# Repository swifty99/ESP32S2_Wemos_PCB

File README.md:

# ESP32S2_Wemos_PCB
Handy adapter to make use of all the IO.
ESP Devices have so many nice interfaces. This PCB adds:
- protection due to dumbness (serial 100Ohms save you electronics big time)
- nice plugs XH plugs work great
- protect against magic smoke from dumb inverse power
- add MosFETs to switch fast and reliable without extra hardwere
- select different power levels for connectors with solder jumpers

This is a Kicad project, feel free to improve. Or just upload the pcb file to the manufacturer you like

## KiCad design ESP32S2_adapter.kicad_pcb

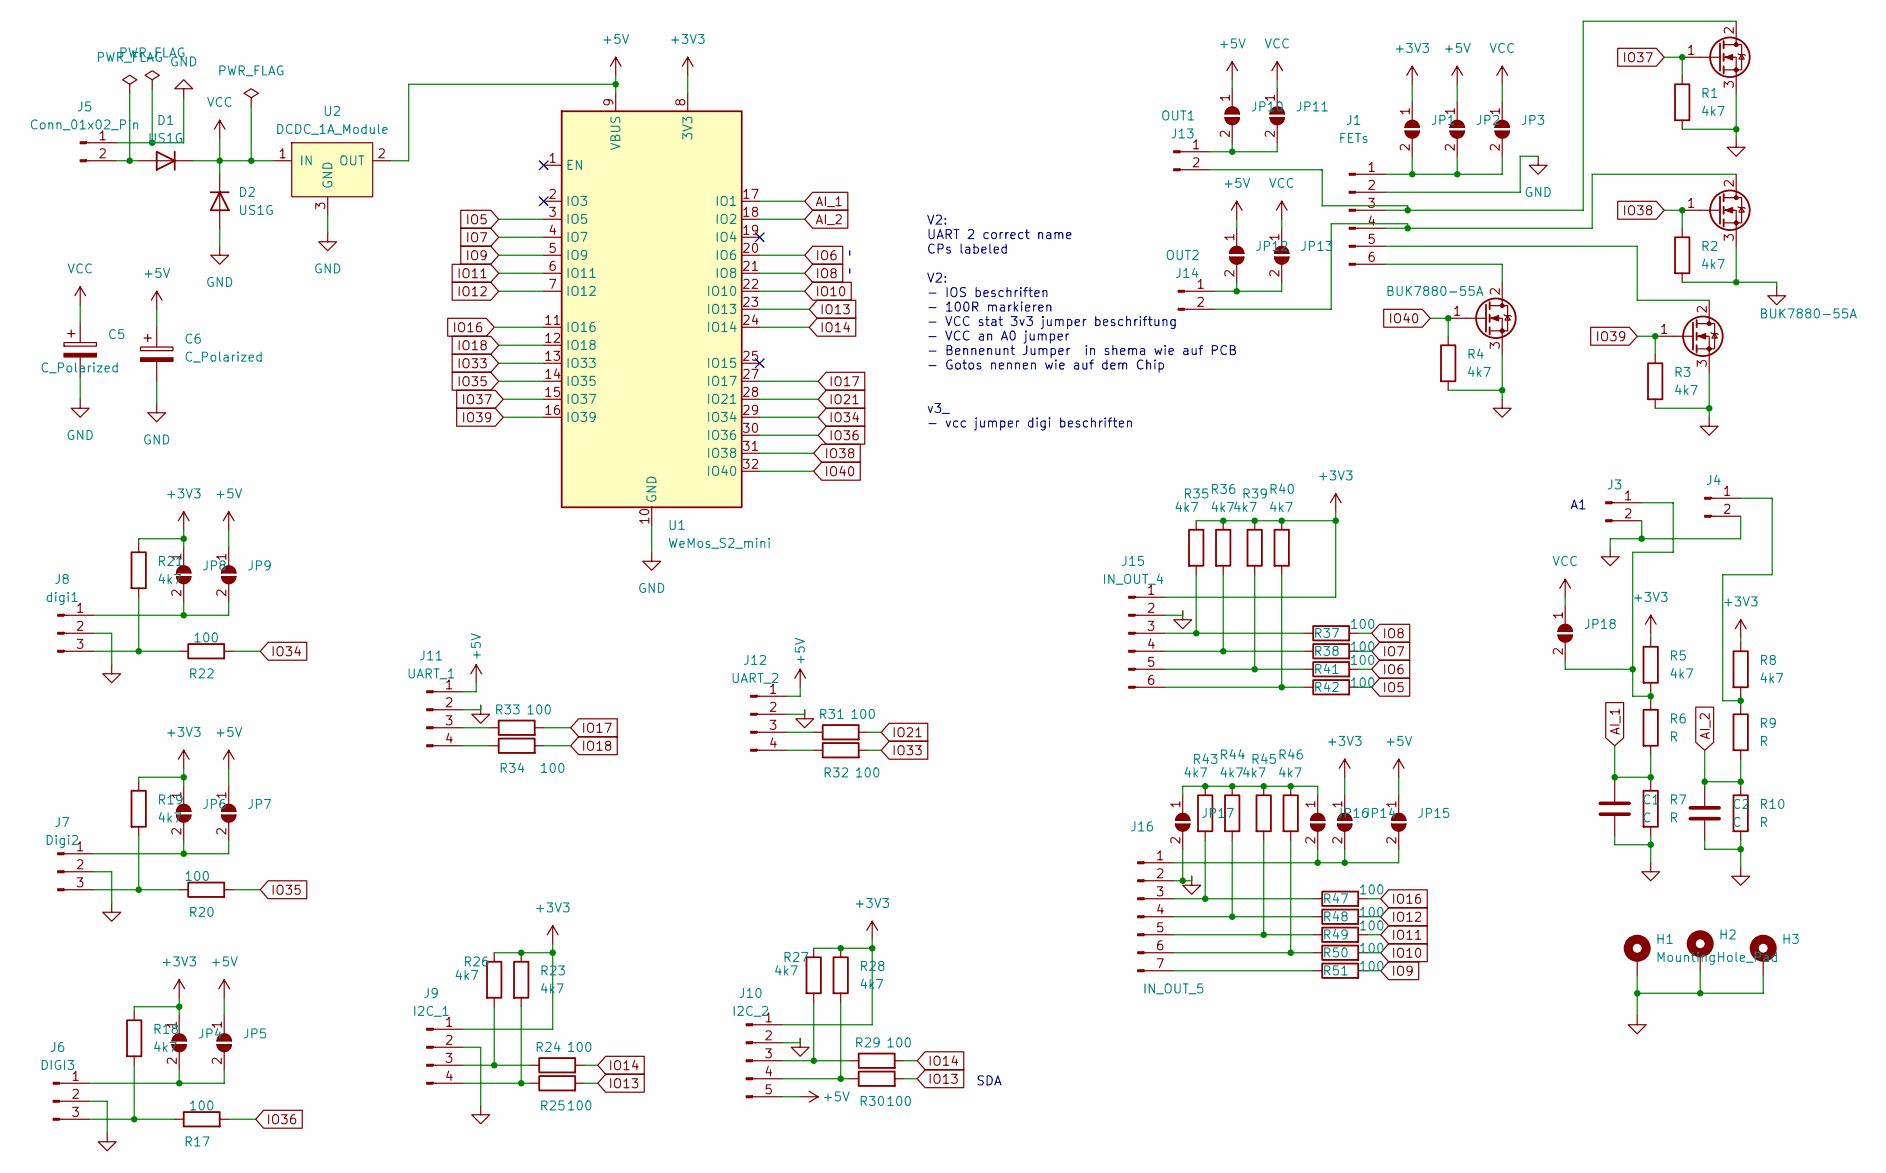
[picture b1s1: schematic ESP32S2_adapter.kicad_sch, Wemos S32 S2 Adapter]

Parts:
C1, C2: C; C_0805_2012Metric_Pad1.18x1.45mm_HandSolder
C5, C6: C_Polarized; CP_Radial_D10.0mm_P3.80mm
D1, D2: US1G; D_SMA_Handsoldering
H1, H2, H3: MountingHole_Pad; MountingHole_3.5mm_Pad_Via
J1: FETs; JST_XH_B6B-XH-A_1x06_P2.50mm_Vertical
J3: A0; JST_XH_B2B-XH-A_1x02_P2.50mm_Vertical
J4: A1; JST_XH_B2B-XH-A_1x02_P2.50mm_Vertical
J5: Conn_01x02_Pin; AMASS_XT30U-M_1x02_P5.0mm_Vertical
J6: DIGI3; JST_XH_B3B-XH-A_1x03_P2.50mm_Vertical
J7: Digi2; JST_XH_B3B-XH-A_1x03_P2.50mm_Vertical
J8: digi1; JST_XH_B3B-XH-A_1x03_P2.50mm_Vertical
J9: I2C_1; JST_XH_B4B-XH-A_1x04_P2.50mm_Vertical
J10: I2C_2; JST_XH_B5B-XH-A_1x05_P2.50mm_Vertical
J11: UART_1; JST_XH_B4B-XH-A_1x04_P2.50mm_Vertical
J12: UART_2; JST_XH_B4B-XH-A_1x04_P2.50mm_Vertical
J13: OUT1; JST_XH_B2B-XH-A_1x02_P2.50mm_Vertical
J14: OUT2; JST_XH_B2B-XH-A_1x02_P2.50mm_Vertical
J15: IN_OUT_4; JST_XH_B6B-XH-A_1x06_P2.50mm_Vertical
J16: IN_OUT_5; JST_XH_B7B-XH-A_1x07_P2.50mm_Vertical
JP1, JP4, JP6, JP8, JP14: 3V3; SolderJumper-2_P1.3mm_Open_TrianglePad1.0x1.5mm
JP2, JP5, JP7, JP9, JP10, JP12, JP15: 5V; SolderJumper-2_P1.3mm_Open_TrianglePad1.0x1.5mm
JP3, JP13, JP18: VCC; SolderJumper-2_P1.3mm_Open_TrianglePad1.0x1.5mm
JP11, JP16: SolderJumper_2_Open; SolderJumper-2_P1.3mm_Open_TrianglePad1.0x1.5mm
JP17: GND; SolderJumper-2_P1.3mm_Open_TrianglePad1.0x1.5mm
Q1, Q2, Q3, Q4: BUK7880-55A; SOT-223-3_TabPin2
R1, R2, R3, R4, R5, R8, R18, R19, R21, R23, R26, R27, R28, R35, R36, R39, R40, R43, R44, R45, R46: 4k7; R_0805_2012Metric_Pad1.20x1.40mm_HandSolder
R6, R7, R9, R10: R; R_0805_2012Metric_Pad1.20x1.40mm_HandSolder
R17, R20, R22, R24, R25, R29, R30, R31, R32, R33, R34, R37, R38, R41, R42, R47, R48, R49, R50, R51: 100; R_0805_2012Metric_Pad1.20x1.40mm_HandSolder
U1: WeMos_S2_mini; WEMOS_S2_mini
U2: DCDC_1A_Module; DCDC_1A_module_bonded

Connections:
+3V3: J9.1, J10.1, J15.1, JP1.1 (A), JP4.1 (A), JP6.1 (A), JP8.1 (A), JP14.1 (A), R5.1, R8.1, R18.1, R19.1, R21.1, R23.1, R26.1, R27.1, R28.1, R35.1, R36.1, R39.1, R40.1, U1.8 (3V3)
+5V: C6.1, J10.5, J11.1, J12.1, JP2.1 (A), JP5.1 (A), JP7.1 (A), JP9.1 (A), JP10.1 (A), JP12.1 (A), JP15.1 (A), U1.9 (VBUS), U2.2 (OUT)
AI_1: C1.1, R6.2, R7.1, U1.17 (IO1)
AI_2: C2.1, R9.2, R10.1, U1.18 (IO2)
GND: C1.2, C2.2, C5.2, C6.2, D2.2 (A), H1.1, H2.1, H3.1, J1.2, J3.2, J4.2, J5.1, J6.2, J7.2, J8.2, J9.2, J10.2, J11.2, J12.2, J15.2, J16.2, JP17.2 (B), Q1.3 (S), Q2.3 (S), Q3.3 (S), Q4.3 (S), R1.2, R2.2, R3.2, R4.2, R7.2, R10.2, U1.10 (GND), U1.26 (GND), U2.3 (GND)
IO5: R42.2, U1.3 (IO5)
IO6: R41.2, U1.20 (IO6)
IO7: R38.2, U1.4 (IO7)
IO8: R37.2, U1.21 (IO8)
IO9: R51.2, U1.5 (IO9)
IO10: R50.2, U1.22 (IO10)
IO11: R49.2, U1.6 (IO11)
IO12: R48.2, U1.7 (IO12)
IO13: R25.2, R30.2, U1.23 (IO13)
IO14: R24.2, R29.2, U1.24 (IO14)
IO16: R47.2, U1.11 (IO16)
IO17: R33.2, U1.27 (IO17)
IO18: R34.2, U1.12 (IO18)
IO21: R31.2, U1.28 (IO21)
IO33: R32.2, U1.13 (IO33)
IO34: R22.2, U1.29 (IO34)
IO35: R20.2, U1.14 (IO35)
IO36: R17.2, U1.30 (IO36)
IO37: Q1.1 (G), R1.1, U1.15 (IO37)
IO38: Q2.1 (G), R2.1, U1.31 (IO38)
IO39: Q3.1 (G), R3.1, U1.16 (IO39)
IO40: Q4.1 (G), R4.1, U1.32 (IO40)
unnamed: D1.2 (A), J5.2
unnamed: J1.1, JP1.2 (B), JP2.2 (B), JP3.2 (B)
unnamed: J1.3, J13.2, Q1.2 (D)
unnamed: J1.4, J14.2, Q2.2 (D)
unnamed: J1.5, Q3.2 (D)
unnamed: J1.6, Q4.2 (D)
unnamed: J3.1, JP18.2 (B), R5.2, R6.1
unnamed: J4.1, R8.2, R9.1
unnamed: J6.1, JP4.2 (B), JP5.2 (B)
unnamed: J6.3, R17.1, R18.2
unnamed: J7.1, JP6.2 (B), JP7.2 (B)
unnamed: J7.3, R19.2, R20.1
unnamed: J8.1, JP8.2 (B), JP9.2 (B)
unnamed: J8.3, R21.2, R22.1
unnamed: J9.3, R24.1, R26.2
unnamed: J9.4, R23.2, R25.1
unnamed: J10.3, R27.2, R29.1
unnamed: J10.4, R28.2, R30.1
unnamed: J11.3, R33.1
unnamed: J11.4, R34.1
unnamed: J12.3, R31.1
unnamed: J12.4, R32.1
unnamed: J13.1, JP10.2 (B), JP11.2 (B)
unnamed: J14.1, JP12.2 (B), JP13.2 (B)
unnamed: J15.3, R35.2, R37.1
unnamed: J15.4, R36.2, R38.1
unnamed: J15.5, R39.2, R41.1
unnamed: J15.6, R40.2, R42.1
unnamed: J16.1, JP14.2 (B), JP15.2 (B), JP16.2 (B)
unnamed: J16.3, R43.2, R47.1
unnamed: J16.4, R44.2, R48.1
unnamed: J16.5, R45.2, R49.1
unnamed: J16.6, R46.2, R50.1
unnamed: J16.7, R51.1
unnamed: JP16.1 (A), JP17.1 (A), R43.1, R44.1, R45.1, R46.1
VCC: C5.1, D1.1 (K), D2.1 (K), JP3.1 (A), JP11.1 (A), JP13.1 (A), JP18.1 (A), U2.1 (IN)

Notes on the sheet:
V2: UART 2 correct name CPs labeled V2: - IOS beschriften - 100R markieren - VCC stat 3v3 jumper beschriftung - VCC an A0 jumper - Bennenunt Jumper in shema wie auf PCB - Gotos nennen wie auf dem Chip v3_ - vcc jumper digi beschriften
SDA

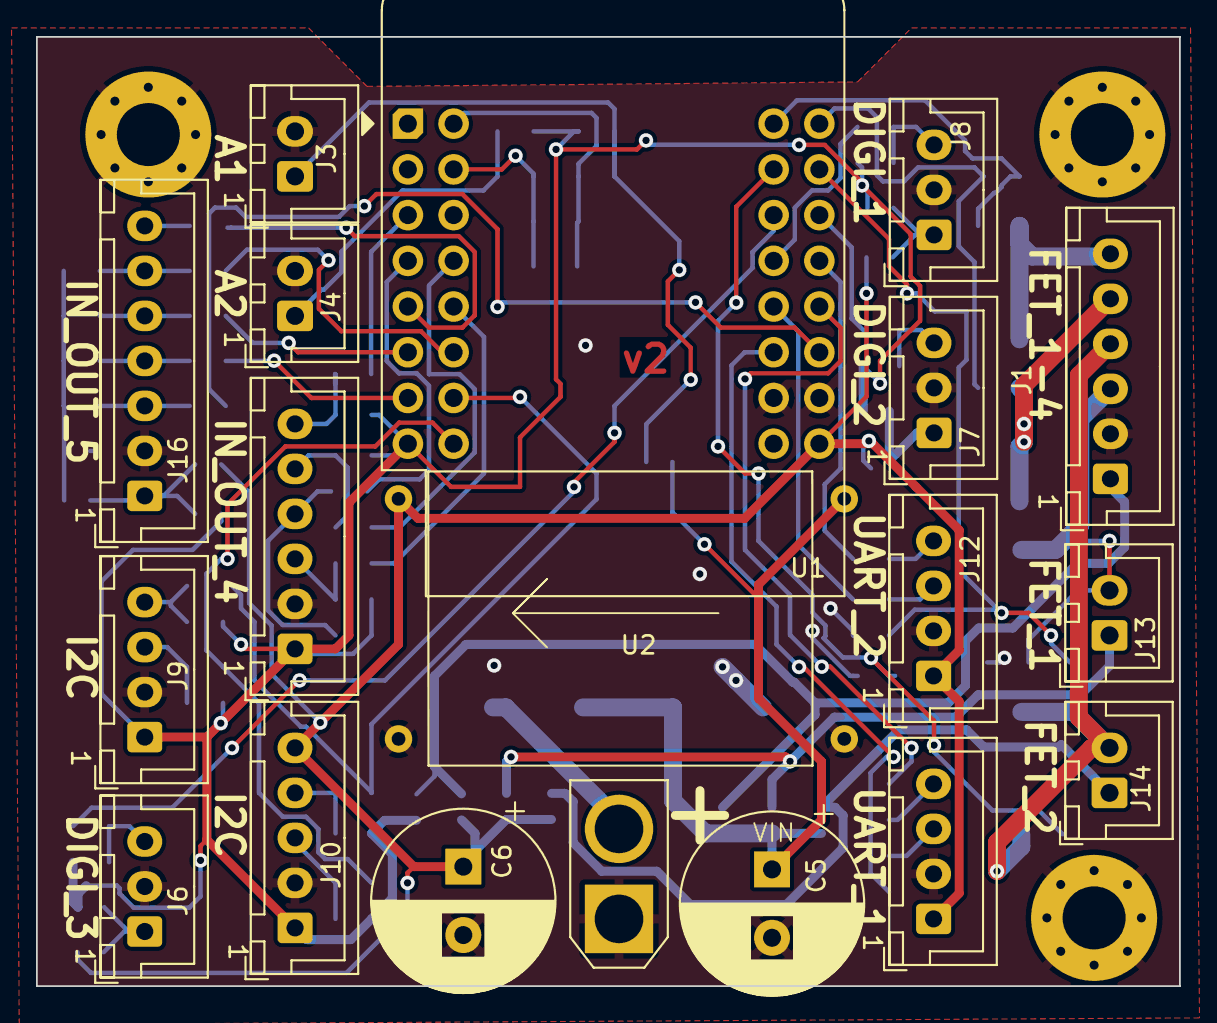
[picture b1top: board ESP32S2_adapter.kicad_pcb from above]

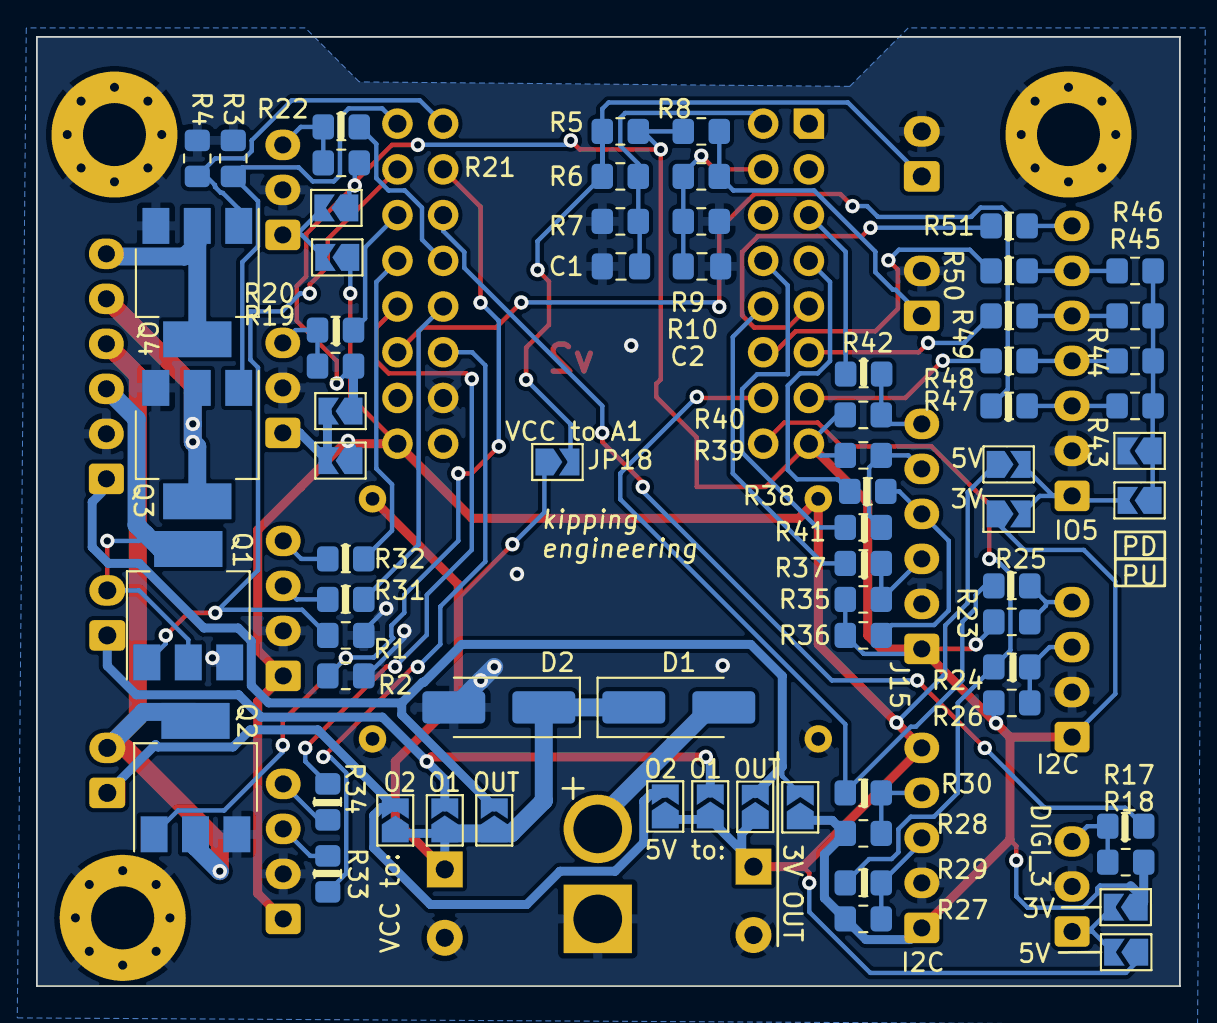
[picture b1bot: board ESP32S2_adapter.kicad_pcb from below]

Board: 2 copper layers, 63.5 x 52.7 mm, 93 parts (71 on the bottom side), 63 nets.

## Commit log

2025-09-10 Add KiCad backup and cache files to .gitignore
2025-09-10 comment update
2025-09-10 3d added
2025-09-10 Enhance README with detailed project information
2025-09-10 Add note on selecting power levels for connectors
2025-09-10 mv files
2025-09-10 Fix image paths in README.md
    Updated image paths for front and rear views.
